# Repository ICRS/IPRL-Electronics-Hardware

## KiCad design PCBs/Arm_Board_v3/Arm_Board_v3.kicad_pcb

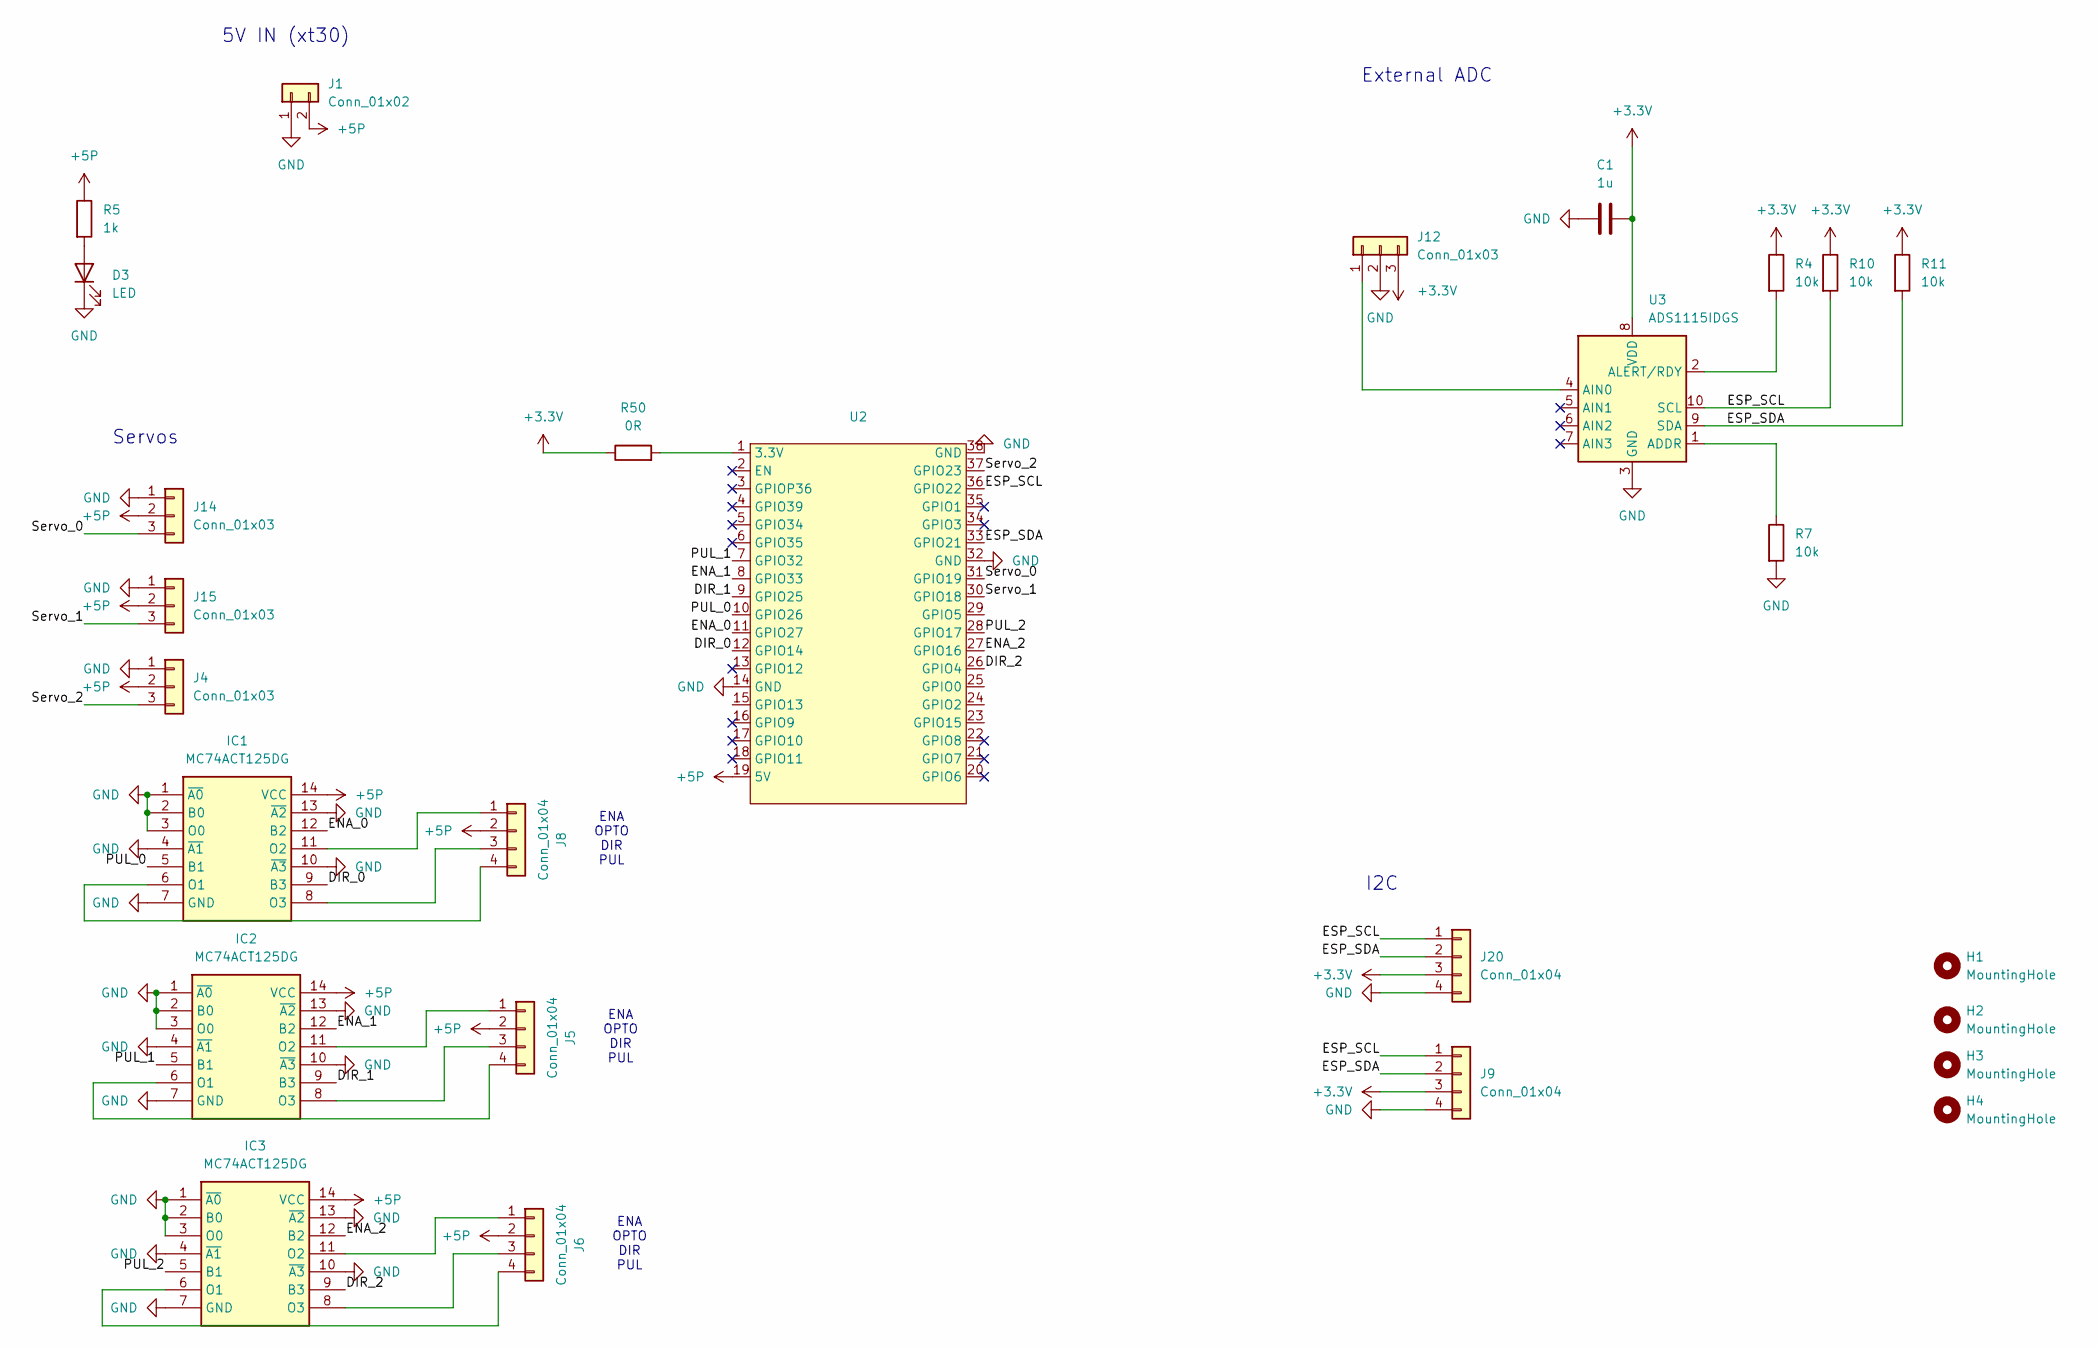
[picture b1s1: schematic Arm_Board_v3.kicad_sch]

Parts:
C1: 1u; C_0805_2012Metric
D3: LED; LED_0805_2012Metric
H1, H2, H3, H4: MountingHole; MountingHole_3.2mm_M3_Pad_TopBottom
IC1, IC2, IC3: MC74ACT125DG; SOIC127P600X175-14N; Manufacturer_Part_Number MC74ACT125DG; Mouser Part Number 863-MC74ACT125DG
J1: Conn_01x02; AMASS_XT30PW-M_1x02_P2.50mm_Horizontal
J4, J12, J14, J15: Conn_01x03; Molex_Micro-Fit_3.0_43045-0400_2x02_P3.00mm_Horizontal
J5, J6, J8, J9, J20: Conn_01x04; Molex_Micro-Fit_3.0_43045-0400_2x02_P3.00mm_Horizontal
R4, R7, R10, R11: 10k; R_0805_2012Metric
R5: 1k; R_0805_2012Metric
R50: 0R; R_0805_2012Metric
U2: Z_ESP32_DevKitC_38pin_socket
U3: ADS1115IDGS; TSSOP-10_3x3mm_P0.5mm

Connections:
+3.3V: C1.2, J9.3, J12.3, J20.3, R4.1, R10.1, R11.1, R50.1, U3.8 (VDD)
+5P: IC1.14 (VCC), IC2.14 (VCC), IC3.14 (VCC), J1.2, J4.2, J5.2, J6.2, J8.2, J14.2, J15.2, R5.1, U2.19 (5V)
/DIR_0: IC1.9 (B3), U2.12 (GPIO14)
/DIR_1: IC2.9 (B3), U2.9 (GPIO25)
/DIR_2: IC3.9 (B3), U2.26 (GPIO4)
/ENA_0: IC1.12 (B2), U2.11 (GPIO27)
/ENA_1: IC2.12 (B2), U2.8 (GPIO33)
/ENA_2: IC3.12 (B2), U2.27 (GPIO16)
/ESP_SCL: J9.1, J20.1, R10.2, U2.36 (GPIO22), U3.10 (SCL)
/ESP_SDA: J9.2, J20.2, R11.2, U2.33 (GPIO21), U3.9 (SDA)
/PUL_0: IC1.5 (B1), U2.10 (GPIO26)
/PUL_1: IC2.5 (B1), U2.7 (GPIO32)
/PUL_2: IC3.5 (B1), U2.28 (GPIO17)
/Servo_0: J14.3, U2.31 (GPIO19)
/Servo_1: J15.3, U2.30 (GPIO18)
/Servo_2: J4.3, U2.37 (GPIO23)
GND: C1.1, D3.1 (K), IC1.1 (~A0), IC1.2 (B0), IC1.3 (O0), IC1.4 (~A1), IC1.7 (GND), IC1.10 (~A3), IC1.13 (~A2), IC2.1 (~A0), IC2.2 (B0), IC2.3 (O0), IC2.4 (~A1), IC2.7 (GND), IC2.10 (~A3), IC2.13 (~A2), IC3.1 (~A0), IC3.2 (B0), IC3.3 (O0), IC3.4 (~A1), IC3.7 (GND), IC3.10 (~A3), IC3.13 (~A2), J1.1, J4.1, J9.4, J12.2, J14.1, J15.1, J20.4, R7.2, U2.14 (GND), U2.32 (GND), U2.38 (GND), U3.3 (GND)
unnamed: D3.2 (A), R5.2
unnamed: IC1.6 (O1), J8.4
unnamed: IC1.11 (O2), J8.1
unnamed: IC1.8 (O3), J8.3
unnamed: IC2.6 (O1), J5.4
unnamed: IC2.11 (O2), J5.1
unnamed: IC2.8 (O3), J5.3
unnamed: IC3.6 (O1), J6.4
unnamed: IC3.11 (O2), J6.1
unnamed: IC3.8 (O3), J6.3
unnamed: J12.1, U3.4 (AIN0)
unnamed: R50.2, U2.1 (3.3V)
unnamed: R7.1, U3.1 (ADDR)
unnamed: R4.2, U3.2 (ALERT/RDY)

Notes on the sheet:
5V IN (xt30)
ENA OPTO DIR PUL
External ADC
I2C
Servos

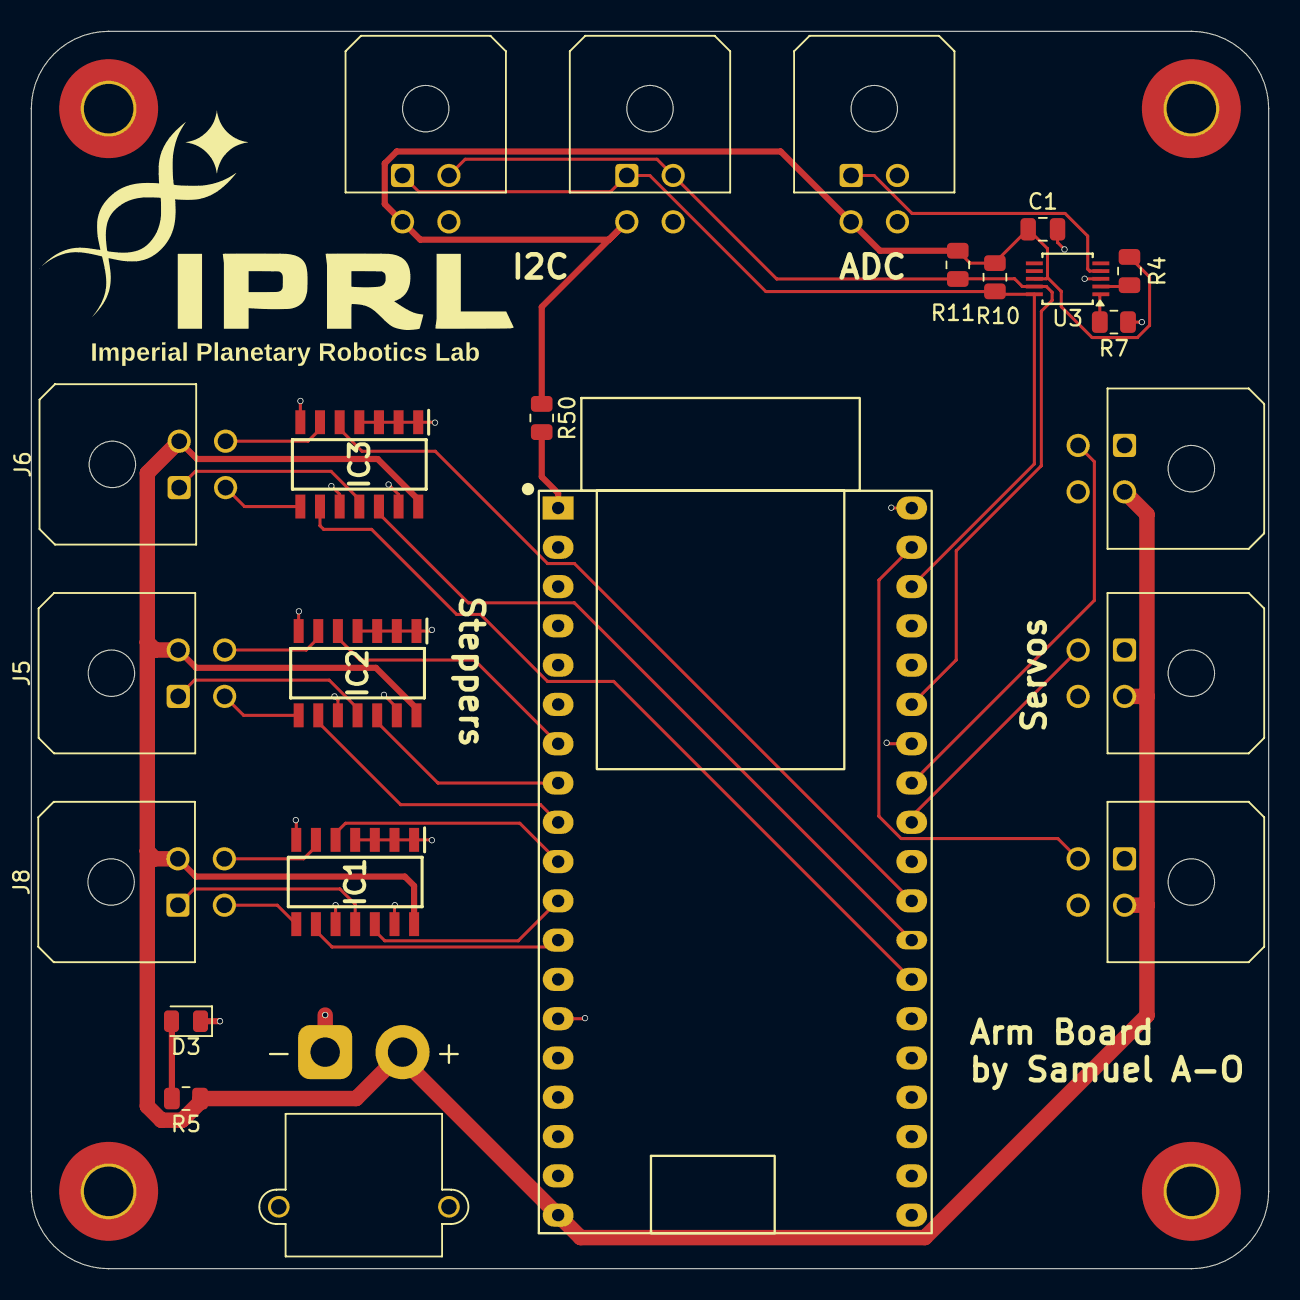
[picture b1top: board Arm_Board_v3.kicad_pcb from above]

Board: 2 copper layers, 80.0 x 80.0 mm, 27 parts (0 on the bottom side), 31 nets.

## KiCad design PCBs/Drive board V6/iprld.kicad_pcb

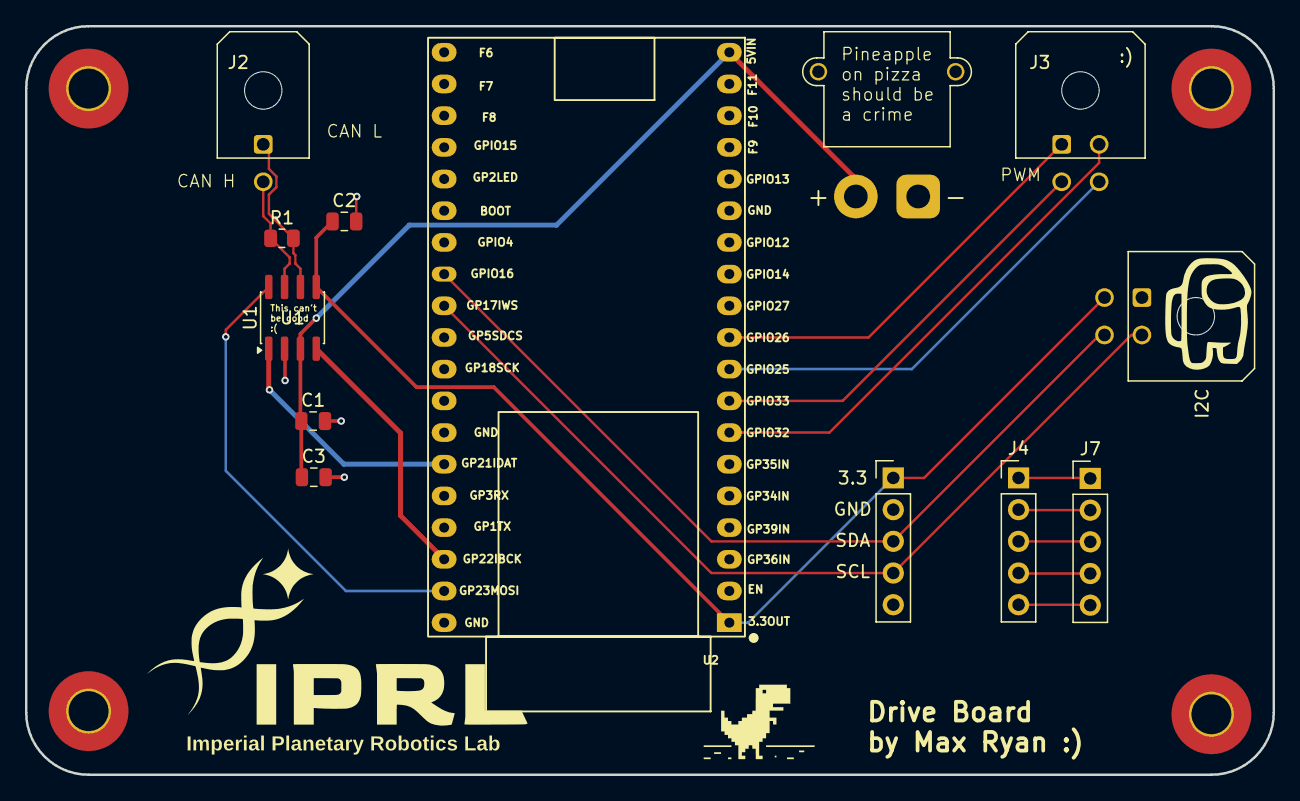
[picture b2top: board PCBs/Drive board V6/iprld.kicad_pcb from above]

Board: 2 copper layers, 100.0 x 60.0 mm, 17 parts (0 on the bottom side), 19 nets.

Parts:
3.3: Conn_01x05; PinHeader_1x05_P2.54mm_Vertical
C1: 1u; C_0805_2012Metric
C2, C3: 0.1u; C_0805_2012Metric
H1, H2, H3, H4: MountingHole; MountingHole_3.2mm_M3_Pad_TopBottom
I2C: Conn_02x02_Top_Bottom; Molex_Micro-Fit_3.0_43045-0400_2x02_P3.00mm_Horizontal
J1: Conn_01x02; AMASS_XT30PW-M_1x02_P2.50mm_Horizontal
J2: Conn_02x01; Molex_Micro-Fit_3.0_43045-0200_2x01_P3.00mm_Horizontal
J3: Conn_02x02_Top_Bottom; Molex_Micro-Fit_3.0_43045-0400_2x02_P3.00mm_Horizontal
J4, J7: Conn_01x05; PinHeader_1x05_P2.54mm_Vertical
R1: 120; R_0805_2012Metric
U1: TJA1051T-3; SOIC-8_3.9x4.9mm_P1.27mm
U2: Z_ESP32_DevKitC_38pin_socket

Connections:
+3.3V: 3.3.1, C2.1, I2C.3, U1.5 (VIO), U2.1 (3.3V)
+5V: C1.1, C3.1, J1.2, U1.3 (VCC), U2.19 (5V)
/CAN_N: J2.1, R1.2, U1.6 (CANL)
/CAN_P: J2.2, R1.1, U1.7 (CANH)
/CAN_RX: U1.4 (RXD), U2.36 (GPIO22)
/CAN_S: U1.8 (S), U2.37 (GPIO23)
/CAN_TX: U1.1 (TXD), U2.33 (GPIO21)
/M1: J3.1, U2.10 (GPIO26)
/M2: J3.2, U2.7 (GPIO32)
/M3: J3.3, U2.8 (GPIO33)
/M4: J3.4, U2.9 (GPIO25)
/SCL: 3.3.4, I2C.2, U2.28 (GPIO17)
/SDA: 3.3.3, I2C.4, U2.27 (GPIO16)
GND: 3.3.2, C1.2, C2.2, C3.2, I2C.1, J1.1, U1.2 (GND), U2.14 (GND), U2.32 (GND), U2.38 (GND)
unnamed: J4.1, J7.1
unnamed: J4.2, J7.2
unnamed: J4.3, J7.3
unnamed: J4.4, J7.4
unnamed: J4.5, J7.5

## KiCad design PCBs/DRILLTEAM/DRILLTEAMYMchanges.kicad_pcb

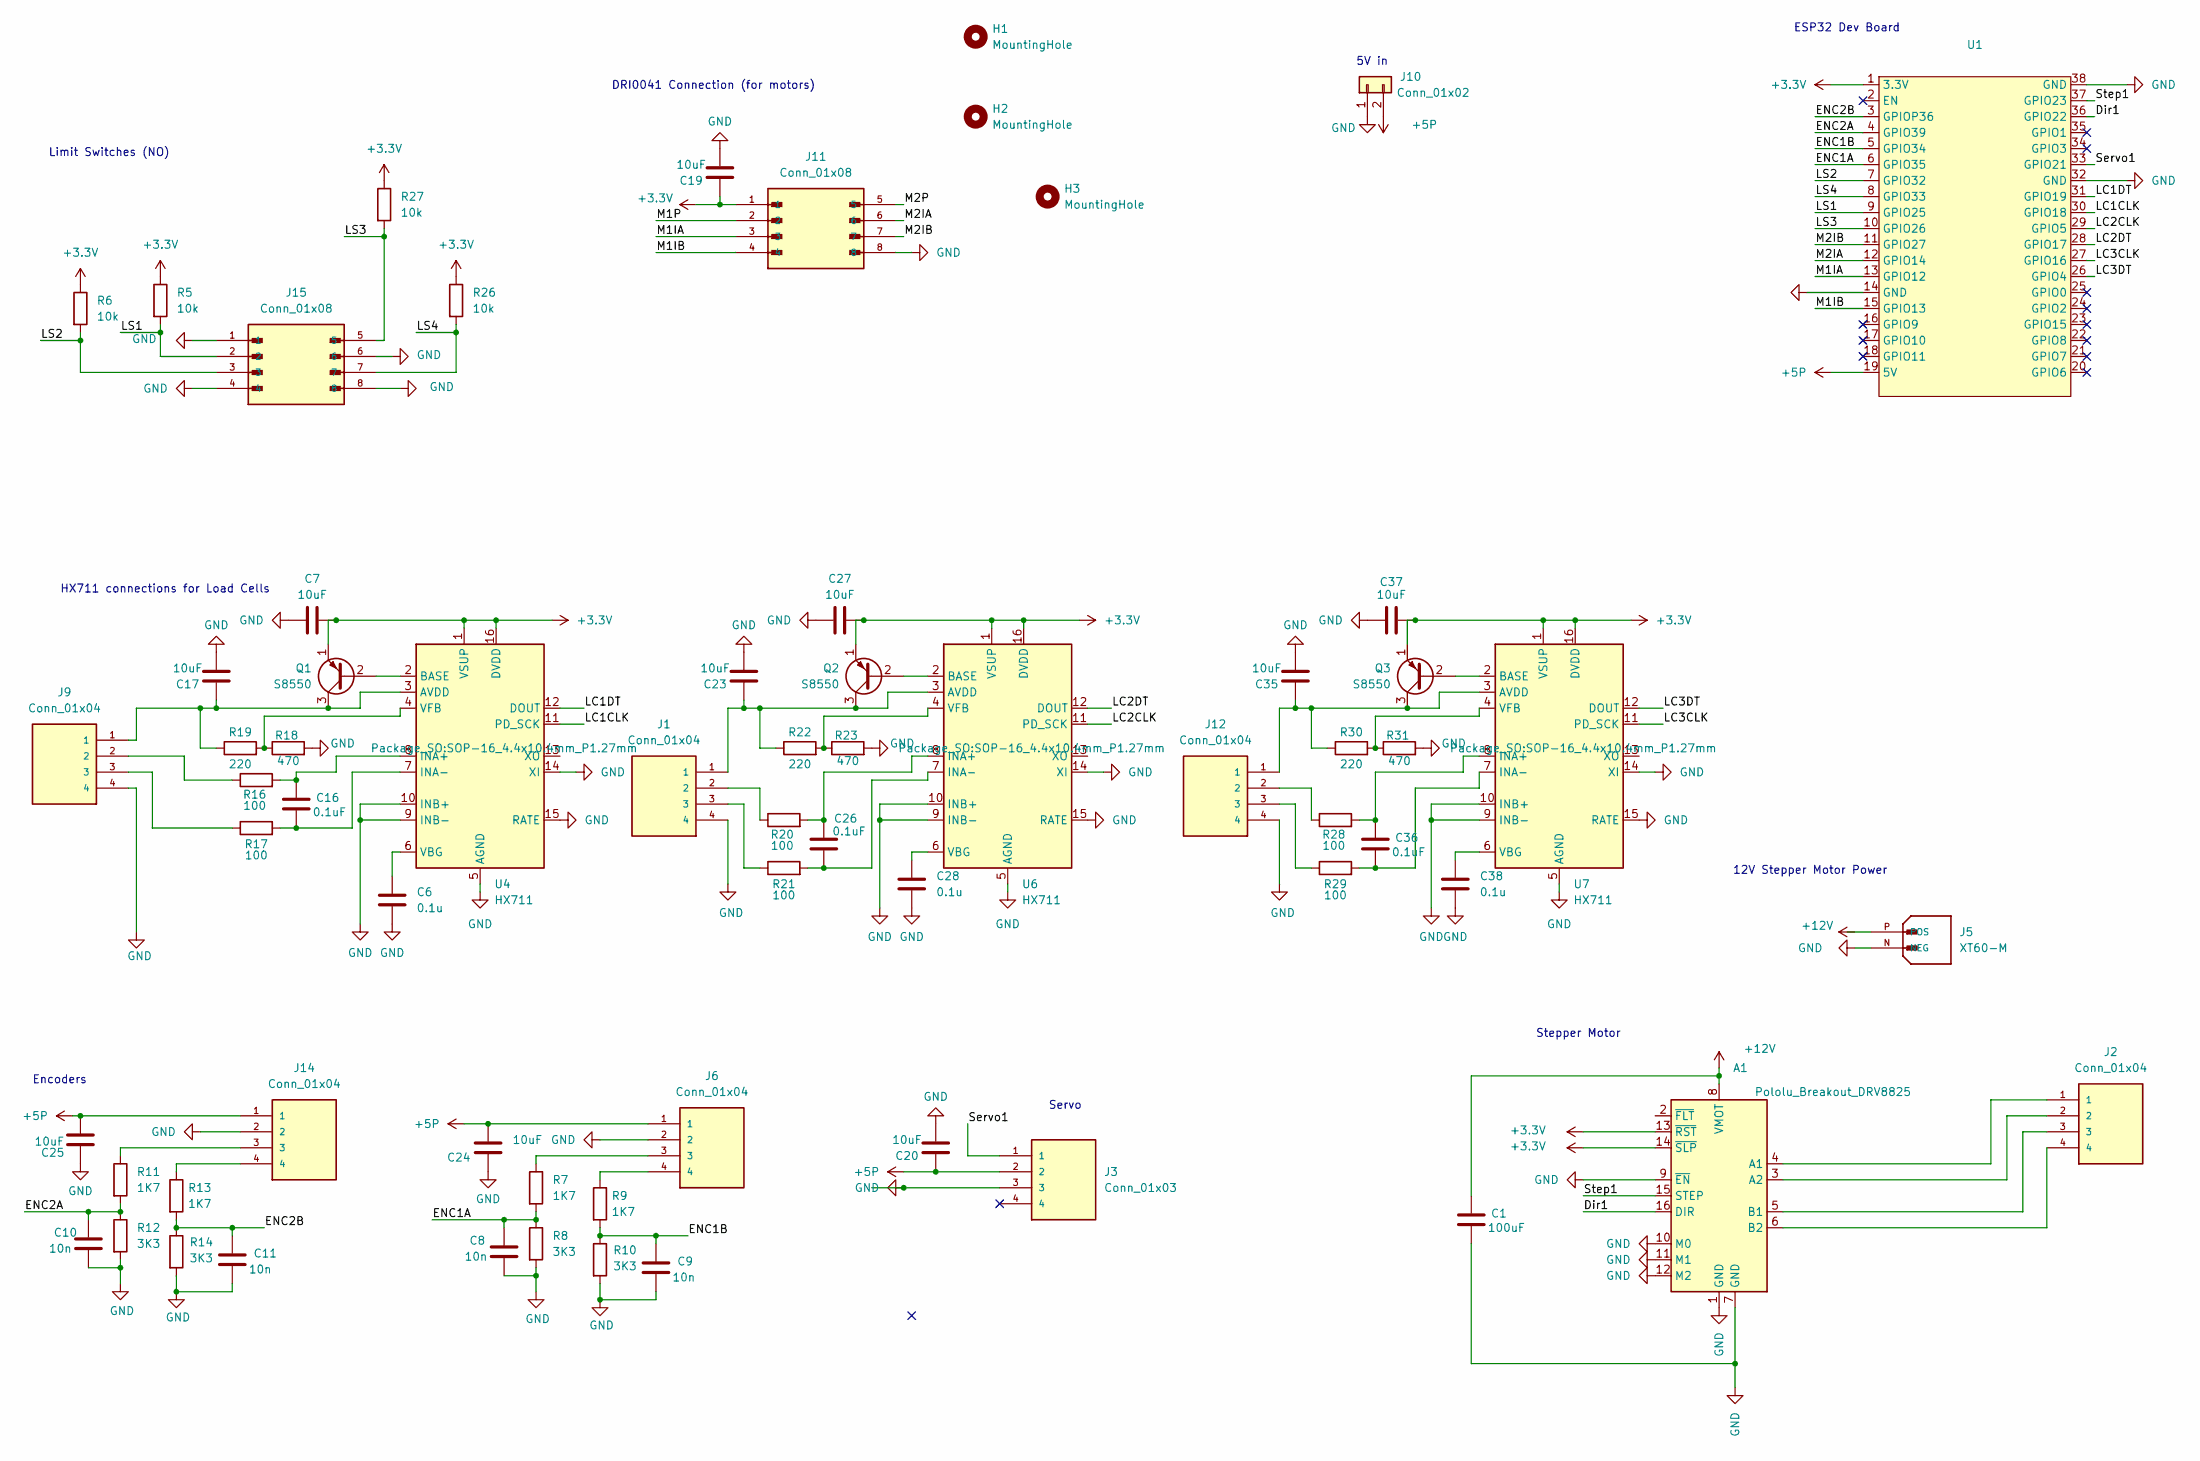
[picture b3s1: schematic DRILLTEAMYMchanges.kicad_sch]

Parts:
A1: Pololu_Breakout_DRV8825; Pololu_Breakout-16_15.2x20.3mm
C1: 100uF; C_0805_2012Metric
C6, C28, C38: 0.1u; C_0805_2012Metric
C7, C17, C19, C20, C23, C24, C25, C27, C35, C37: 10uF; C_0805_2012Metric
C8, C9, C10, C11: 10n; C_0805_2012Metric
C16, C26, C36: 0.1uF; C_0805_2012Metric
H1, H2, H3: MountingHole; MountingHole_3.2mm_M3
J1, J12: Conn_01x04; MOLEX_430450400; PARTREV D7
J2, J6, J9, J14: Conn_01x04; MOLEX_430450400; PARTREV G
J3: Conn_01x03; MOLEX_430450400; PARTREV G
J5: XT60-M; AMASS_XT60-M; PARTREV V1.2
J10: Conn_01x02; AMASS_XT30PW-M_1x02_P2.50mm_Horizontal
J11, J15: Conn_01x08; MOLEX_430450800; PARTREV G
Q1, Q2, Q3: S8550; TO-92_Inline
R5, R6, R26, R27: 10k; R_0805_2012Metric
R7, R9, R11, R13: 1K7; R_0805_2012Metric
R8, R10, R12, R14: 3K3; R_0805_2012Metric
R16, R17, R20, R21, R28, R29: 100; R_0805_2012Metric
R18, R23, R31: 470; R_0805_2012Metric
R19, R22, R30: 220; R_0805_2012Metric
U1: Z_ESP32_DevKitC_38pin_socket
U4, U6, U7: HX711; SOP-16_4.4x10.4mm_P1.27mm

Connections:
+3.3V: A1.13 (~RST), A1.14 (~SLP), C7.2, C19.2, C27.2, C37.2, J11.1, Q1.1 (E), Q2.1 (E), Q3.1 (E), R5.1, R6.1, R26.1, R27.1, U1.1 (3.3V), U4.1 (VSUP), U4.16 (DVDD), U6.1 (VSUP), U6.16 (DVDD), U7.1 (VSUP), U7.16 (DVDD)
+5P: C20.2, C24.2, C25.2, J3.2, J6.1, J10.2, J14.1, U1.19 (5V)
+12V: A1.8 (VMOT), C1.1, J5.P (POS)
/Dir1: A1.16 (DIR), U1.36 (GPIO22)
/ENC1A: C8.1, R7.2, R8.1, U1.6 (GPIO35)
/ENC1B: C9.1, R9.2, R10.1, U1.5 (GPIO34)
/ENC2A: C10.1, R11.2, R12.1, U1.4 (GPIO39)
/ENC2B: C11.1, R13.2, R14.1, U1.3 (GPIOP36)
/LC1CLK: U1.30 (GPIO18), U4.11 (PD_SCK)
/LC1DT: U1.31 (GPIO19), U4.12 (DOUT)
/LC2CLK: U1.29 (GPIO5), U6.11 (PD_SCK)
/LC2DT: U1.28 (GPIO17), U6.12 (DOUT)
/LC3CLK: U1.27 (GPIO16), U7.11 (PD_SCK)
/LC3DT: U1.26 (GPIO4), U7.12 (DOUT)
/LS1: J15.2, R5.2, U1.9 (GPIO25)
/LS2: J15.3, R6.2, U1.7 (GPIO32)
/LS3: J15.5, R27.2, U1.10 (GPIO26)
/LS4: J15.7, R26.2, U1.8 (GPIO33)
/M1IA: J11.3, U1.13 (GPIO12)
/M1IB: J11.4, U1.15 (GPIO13)
/M1P: J11.2
/M2IA: J11.6, U1.12 (GPIO14)
/M2IB: J11.7, U1.11 (GPIO27)
/M2P: J11.5
/Servo1: J3.1, U1.33 (GPIO21)
/Step1: A1.15 (STEP), U1.37 (GPIO23)
GND: A1.1 (GND), A1.7 (GND), A1.9 (~EN), A1.10 (M0), A1.11 (M1), A1.12 (M2), C1.2, C6.2, C7.1, C8.2, C9.2, C10.2, C11.2, C17.1, C19.1, C20.1, C23.1, C24.1, C25.1, C27.1, C28.2, C35.1, C37.1, C38.2, J1.4, J3.3, J5.N (NEG), J6.2, J9.4, J10.1, J11.8, J12.4, J14.2, J15.1, J15.4, J15.6, J15.8, R8.2, R10.2, R12.2, R14.2, R18.2, R23.2, R31.2, U1.14 (GND), U1.32 (GND), U1.38 (GND), U4.5 (AGND), U4.9 (INB-), U4.10 (INB+), U4.14 (XI), U4.15 (RATE), U6.5 (AGND), U6.9 (INB-), U6.10 (INB+), U6.14 (XI), U6.15 (RATE), U7.5 (AGND), U7.9 (INB-), U7.10 (INB+), U7.14 (XI), U7.15 (RATE)
unnamed: A1.4 (A1), J2.1
unnamed: A1.3 (A2), J2.2
unnamed: A1.5 (B1), J2.3
unnamed: A1.6 (B2), J2.4
unnamed: J1.2, R20.1
unnamed: J1.3, R21.1
unnamed: J6.3, R7.1
unnamed: J6.4, R9.1
unnamed: J9.2, R16.1
unnamed: J9.3, R17.1
unnamed: J12.2, R28.1
unnamed: J12.3, R29.1
unnamed: J14.3, R11.1
unnamed: J14.4, R13.1
unnamed: Q1.2 (B), U4.2 (BASE)
unnamed: C17.2, J9.1, Q1.3 (C), R19.1, U4.3 (AVDD)
unnamed: Q2.2 (B), U6.2 (BASE)
unnamed: C23.2, J1.1, Q2.3 (C), R22.1, U6.3 (AVDD)
unnamed: Q3.2 (B), U7.2 (BASE)
unnamed: C35.2, J12.1, Q3.3 (C), R30.1, U7.3 (AVDD)
unnamed: C16.1, R16.2, U4.8 (INA+)
unnamed: C16.2, R17.2, U4.7 (INA-)
unnamed: C6.1, U4.6 (VBG)
unnamed: R18.1, R19.2, U4.4 (VFB)
unnamed: C26.1, R20.2, U6.8 (INA+)
unnamed: C26.2, R21.2, U6.7 (INA-)
unnamed: C28.1, U6.6 (VBG)
unnamed: R22.2, R23.1, U6.4 (VFB)
unnamed: C36.1, R28.2, U7.8 (INA+)
unnamed: C36.2, R29.2, U7.7 (INA-)
unnamed: C38.1, U7.6 (VBG)
unnamed: R30.2, R31.1, U7.4 (VFB)

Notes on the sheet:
DRI0041 Connection (for motors)
Servo
Encoders
5V in
Limit Switches (NO)
ESP32 Dev Board
Stepper Motor
HX711 connections for Load Cells
12V Stepper Motor Power

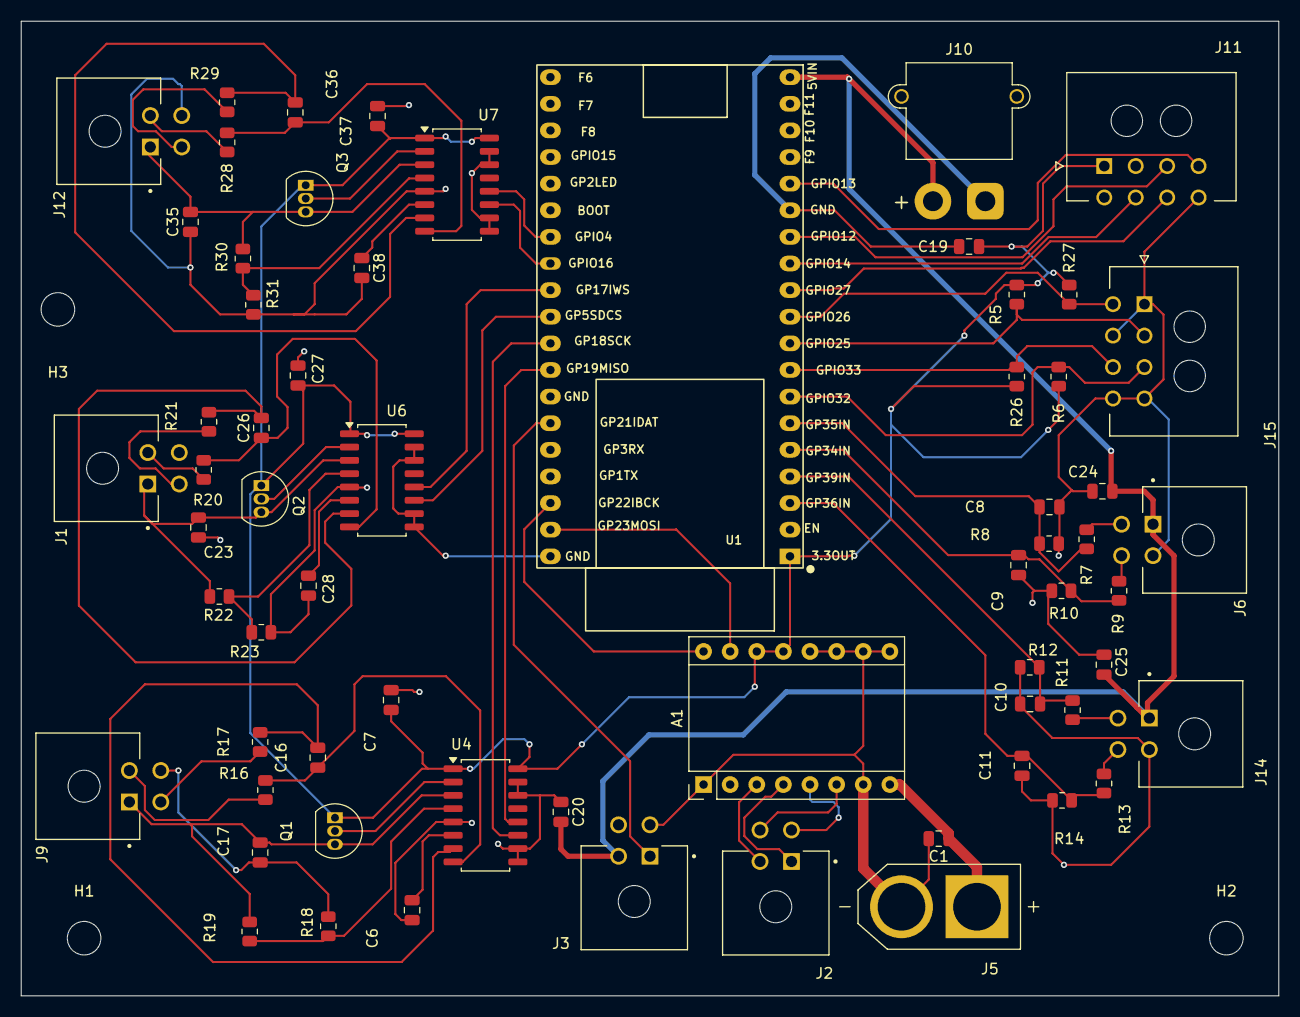
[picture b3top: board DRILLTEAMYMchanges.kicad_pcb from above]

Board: 2 copper layers, 120.0 x 93.0 mm, 67 parts (0 on the bottom side), 57 nets.
